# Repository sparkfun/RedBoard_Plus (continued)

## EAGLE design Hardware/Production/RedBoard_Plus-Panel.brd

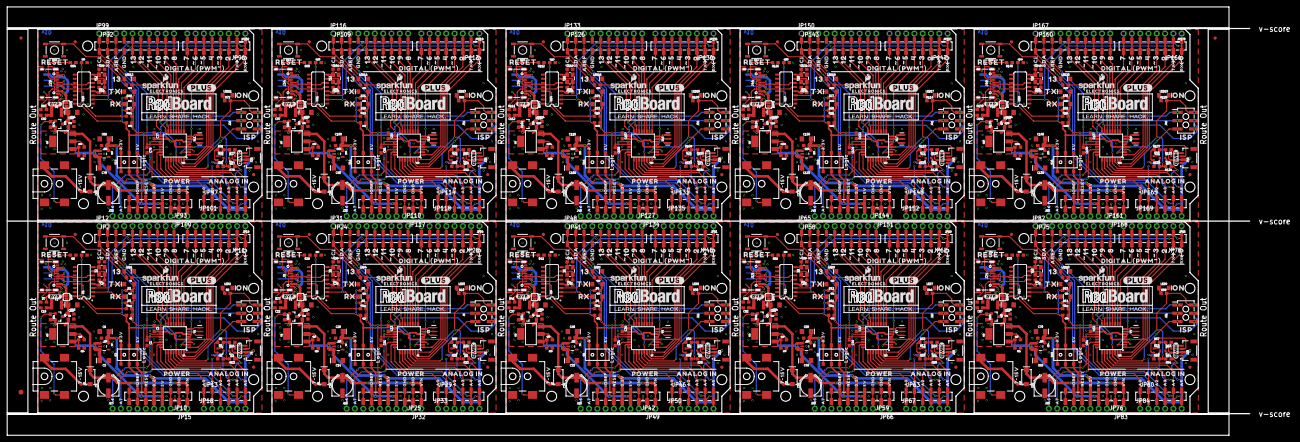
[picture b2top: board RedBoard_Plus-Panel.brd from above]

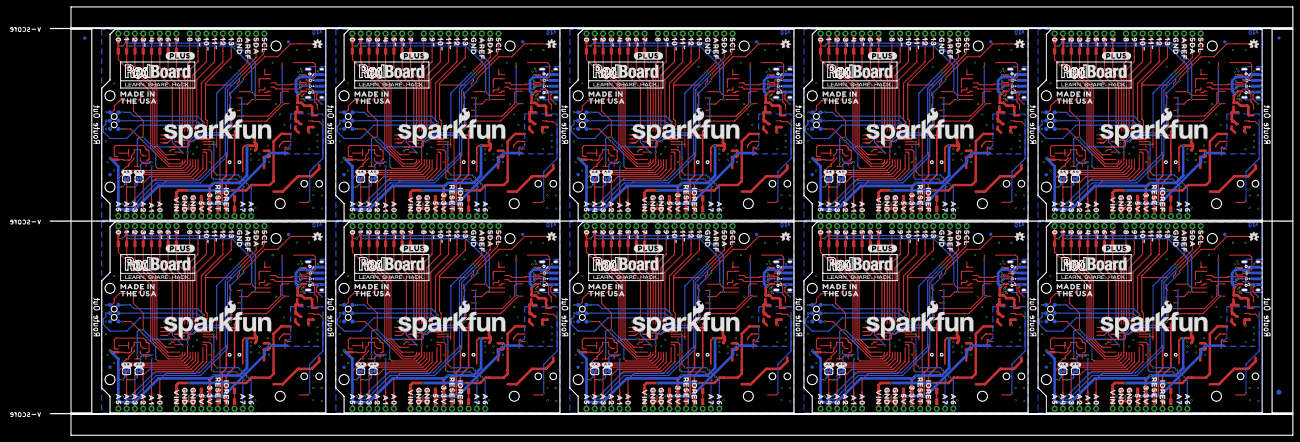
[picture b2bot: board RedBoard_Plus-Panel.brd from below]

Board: 2 copper layers, 380.2 x 131.1 mm, 1786 parts (573 on the bottom side), 530 nets.

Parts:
BYP, BYP1, BYP2, BYP3, BYP4, BYP5, BYP6, BYP7, BYP8, BYP9: JUMPER-SMT_2_NO_SILK; SMT-JUMPER_2_NO_SILK
C1, C2, C4, C8, C10, C11, C12, C13, C18, C19, C21, C22, C23, C28, C31, C32, C34, C36, C37, C38, C43, C46, C47, C49, C51, C52, C53, C58, C61, C62, C64, C66, C67, C68, C73, C76, C77, C79, C81, C82, C83, C88, C91, C92, C94, C96, C97, C98, C103, C106, C107, C109, C111, C112, C113, C118, C121, C122, C124, C126, C127, C128, C133, C136, C137, C139, C141, C142, C143, C148: 0.1uF; 0603
C3, C6, C14, C15, C24, C25, C33, C39, C40, C48, C54, C55, C63, C69, C70, C78, C84, C85, C93, C99, C100, C108, C114, C115, C123, C129, C130, C138, C144, C145: 10uF; EIA3216
C5, C20, C35, C50, C65, C80, C95, C110, C125, C140: 47uF; PANASONIC_D
C7, C9, C29, C30, C44, C45, C59, C60, C74, C75, C89, C90, C104, C105, C119, C120, C134, C135, C149, C150: 10pF; 0603
C16, C26, C41, C56, C71, C86, C101, C116, C131, C146: 1.0uF; 0603
C17, C27, C42, C57, C72, C87, C102, C117, C132, C147: 10nF; 0603
D1, D4, D7, D10, D13, D16, D19, D22, D25, D28: 1A/40V/500mV; SMA-DIODE
D2, D6, D9, D12, D15, D18, D21, D24, D27, D30: GREEN; LED-1206
D3, D5, D8, D11, D14, D17, D20, D23, D26, D29: YELLOW; LED-1206-HIDDENSILK
E$1, E$2, E$3, E$4: FIDUCIAL-1X2
E$5, E$6: FIDUCIAL-1.5X3
F1, F2, F3, F4, F5, F6, F7, F8, F9, F10: 6V/2A; 1210
FD1, FD2, FD3, FD4, FD5, FD6, FD7, FD8, FD9, FD10, FD11, FD12, FD13, FD14, FD15, FD16, FD17, FD18, FD19, FD20: FIDUCIAL1X2; FIDUCIAL-1X2
IC1, IC2, IC3, IC4, IC5, IC6, IC7, IC8, IC9, IC10: LM1117; SOT223
J1, J10, J15, J20, J25, J30, J35, J40, J45, J50: DNP; 1X02_NO_SILK
J2, J6, J11, J16, J21, J26, J31, J36, J41, J46: ISP; 2X3_SMT_POSTS
J3, J7, J12, J17, J22, J27, J32, J37, J42, J47: 5.5x2.1mm Barrel; POWER_JACK_SMD
J4, J8, J13, J18, J23, J28, J33, J38, J43, J48: QWIIC_RIGHT_ANGLE; JST04_1MM_RA
J5, J9, J14, J19, J24, J29, J34, J39, J44, J49: USB Female Type C Connector; USB-C-16P-2LAYER-PADS
JP1, JP26, JP43, JP60, JP77, JP94, JP111, JP128, JP145, JP162: SFE_LOGO_NAME.1_INCH; SFE_LOGO_NAME_.1
JP2, JP24, JP41, JP58, JP75, JP92, JP109, JP126, JP143, JP160: 1X10_SMD_COMBINED
JP3, JP4, JP5, JP6, JP16, JP17, JP20, JP21, JP35, JP36, JP37, JP38, JP52, JP53, JP54, JP55, JP69, JP70, JP71, JP72, JP86, JP87, JP88, JP89, JP103, JP104, JP105, JP106, JP120, JP121, JP122, JP123, JP137, JP138, JP139, JP140, JP154, JP155, JP156, JP157: STAND-OFFTIGHT; STAND-OFF-TIGHT
JP7, JP27, JP44, JP61, JP78, JP95, JP112, JP129, JP146, JP163: SFE_LOGO_FLAME.1_INCH; SFE_LOGO_FLAME_.1
JP8, JP9, JP22, JP23, JP39, JP40, JP56, JP57, JP73, JP74, JP90, JP91, JP107, JP108, JP124, JP125, JP141, JP142, JP158, JP159: FIDUCIAL1X2; FIDUCIAL-1X2
JP10, JP25, JP42, JP59, JP76, JP93, JP110, JP127, JP144, JP161: 1X08_SMD_COMBINED
JP11, JP28, JP45, JP62, JP79, JP96, JP113, JP130, JP147, JP164: JP11; 1X08_SMD_COMBINED
JP12, JP31, JP48, JP65, JP82, JP99, JP116, JP133, JP150, JP167: DNP; 1X10_NO_SILK
JP13, JP29, JP46, JP63, JP80, JP97, JP114, JP131, JP148, JP165: 1X06_SMD_STRAIGHT_COMBO
JP14, JP30, JP47, JP64, JP81, JP98, JP115, JP132, JP149, JP166: USB_SOLDER_PADS; USB-SOLDER-PADS
JP15, JP19, JP32, JP34, JP49, JP51, JP66, JP68, JP83, JP85, JP100, JP102, JP117, JP119, JP134, JP136, JP151, JP153, JP168, JP170: DNP; 1X08_NO_SILK
JP18, JP33, JP50, JP67, JP84, JP101, JP118, JP135, JP152, JP169: DNP; 1X06_NO_SILK
LED1, LED4, LED6, LED8, LED10, LED12, LED14, LED16, LED18, LED20: Blue; LED-1206-HIDDENSILK
LED2, LED3, LED5, LED7, LED9, LED11, LED13, LED15, LED17, LED19: GREEN; LED-1206
LOGO1, LOGO2, LOGO3, LOGO4, LOGO5, LOGO6, LOGO7, LOGO8, LOGO9, LOGO10: QWIIC_LOGO_5MM; QWIIC_5MM
Q1, Q4, Q7, Q10, Q13, Q16, Q19, Q22, Q25, Q28: 20V/4.2A/52mΩ/1.4W; SOT23-3
Q2, Q3, Q5, Q6, Q8, Q9, Q11, Q12, Q14, Q15, Q17, Q18, Q20, Q21, Q23, Q24, Q26, Q27, Q29, Q30: 310mA/60V/1.6Ω; SOT323
QW1, QW2, QW3, QW4, QW5, QW6, QW7, QW8, QW9, QW10, QW11, QW12, QW13, QW14, QW15, QW16, QW17, QW18, QW19, QW20: JUMPER-SMT_2_NC_TRACE_SILK; SMT-JUMPER_2_NC_TRACE_SILK
R1, R9, R12, R16, R23, R24, R29, R37, R38, R43, R51, R52, R57, R65, R66, R71, R79, R80, R85, R93, R94, R99, R107, R108, R113, R121, R122, R127, R135, R136: 4.7k; 0603
R2, R3, R4, R10, R17, R18, R30, R31, R32, R44, R45, R46, R58, R59, R60, R72, R73, R74, R86, R87, R88, R100, R101, R102, R114, R115, R116, R128, R129, R130: 10k; 0603
R5, R6, R11, R13, R21, R22, R25, R26, R35, R36, R39, R40, R49, R50, R53, R54, R63, R64, R67, R68, R77, R78, R81, R82, R91, R92, R95, R96, R105, R106, R109, R110, R119, R120, R123, R124, R133, R134, R137, R138: 2.2k; 0603
R7, R8, R27, R28, R41, R42, R55, R56, R69, R70, R83, R84, R97, R98, R111, R112, R125, R126, R139, R140: 5.1k; 0603
R14, R19, R33, R47, R61, R75, R89, R103, R117, R131: 715; 0603
R15, R20, R34, R48, R62, R76, R90, R104, R118, R132: 240; 0603
S1, S3, S5, S7, S9, S11, S13, S15, S17, S19: Tall Switch; TACTILE_SWITCH_SMD_5.2MM
S2, S4, S6, S8, S10, S12, S14, S16, S18, S20: SWITCH_DPDT_SMD_AYZ0202
TP1, TP2, TP3, TP4, TP5, TP6, TP7, TP8, TP9, TP10, TP11, TP12, TP13, TP14, TP15, TP16, TP17, TP18, TP19, TP20, TP21, TP22, TP23, TP24, TP25, TP26, TP27, TP28, TP29, TP30, TP31, TP32, TP33, TP34, TP35, TP36, TP37, TP38, TP39, TP40, TP41, TP42, TP43, TP44, TP45, TP46, TP47, TP48, TP49, TP50, TP51, TP52, TP53, TP54, TP55, TP56, TP57, TP58, TP59, TP60: TP-3x5; PAD.03X.05
U1, U6, U9, U12, U15, U18, U21, U24, U27, U30: CH340G; SO016
U2, U4, U7, U10, U13, U16, U19, U22, U25, U28: ATMEGA328P_TQFP; TQFP32-08
U3, U5, U8, U11, U14, U17, U20, U23, U26, U29: 3.3V; SOT23-5
U$1, U$3, U$164, U$165, U$262, U$263, U$360, U$361, U$458, U$459, U$556, U$557, U$654, U$655, U$752, U$753, U$850, U$851, U$948, U$949: REDBOARD_LOGO
U$2, U$162, U$260, U$358, U$456, U$554, U$652, U$750, U$848, U$946: _D#0
U$4, U$160, U$258, U$356, U$454, U$552, U$650, U$748, U$846, U$944: V0
U$5, U$16, U$197, U$295, U$393, U$491, U$589, U$687, U$785, U$883: OSHW-LOGOS; OSHW-LOGO-S
U$6, U$14, U$198, U$296, U$394, U$492, U$590, U$688, U$786, U$884: #BYP#0
U$7, U$17, U$199, U$297, U$395, U$493, U$591, U$689, U$787, U$885: 7#15V0
U$8, U$22, U$77, U$154, U$200, U$252, U$298, U$350, U$396, U$448, U$494, U$546, U$592, U$644, U$690, U$742, U$788, U$840, U$886, U$938: 130
U$9, U$195, U$293, U$391, U$489, U$587, U$685, U$783, U$881, U$979: 10#0
U$10, U$163, U$261, U$359, U$457, U$555, U$653, U$751, U$849, U$947: G0
U$11, U$190, U$288, U$386, U$484, U$582, U$680, U$778, U$876, U$974: LOGIC0
U$12, U$161, U$259, U$357, U$455, U$553, U$651, U$749, U$847, U$945: D#0
U$13, U$95, U$177, U$181, U$275, U$279, U$373, U$377, U$471, U$475, U$569, U$573, U$667, U$671, U$765, U$769, U$863, U$867, U$961, U$965: _RESET0
U$15, U$23, U$76, U$153, U$201, U$251, U$299, U$349, U$397, U$447, U$495, U$545, U$593, U$643, U$691, U$741, U$789, U$839, U$887, U$937: 120
U$18, U$182, U$280, U$378, U$476, U$574, U$672, U$770, U$868, U$966: _AREF0
U$19, U$183, U$281, U$379, U$477, U$575, U$673, U$771, U$869, U$967: _SCL0
U$20, U$184, U$282, U$380, U$478, U$576, U$674, U$772, U$870, U$968: _SDA0
U$21, U$196, U$294, U$392, U$490, U$588, U$686, U$784, U$882, U$980: 11#0
U$24, U$74, U$202, U$300, U$398, U$496, U$594, U$692, U$790, U$888: #110
U$25, U$75, U$203, U$301, U$399, U$497, U$595, U$693, U$791, U$889: #100
U$26, U$91, U$204, U$302, U$400, U$498, U$596, U$694, U$792, U$890: #90
U$27, U$72, U$92, U$151, U$205, U$249, U$303, U$347, U$401, U$445, U$499, U$543, U$597, U$641, U$695, U$739, U$793, U$837, U$891, U$935: 80
U$28, U$71, U$108, U$150, U$206, U$248, U$304, U$346, U$402, U$444, U$500, U$542, U$598, U$640, U$696, U$738, U$794, U$836, U$892, U$934: 70
U$29, U$109, U$207, U$305, U$403, U$501, U$599, U$697, U$795, U$893: #60
U$30, U$110, U$208, U$306, U$404, U$502, U$600, U$698, U$796, U$894: #50
U$31, U$68, U$111, U$147, U$209, U$245, U$307, U$343, U$405, U$441, U$503, U$539, U$601, U$637, U$699, U$735, U$797, U$833, U$895, U$931: 40
U$32, U$112, U$210, U$308, U$406, U$504, U$602, U$700, U$798, U$896: #30
U$33, U$66, U$113, U$145, U$211, U$243, U$309, U$341, U$407, U$439, U$505, U$537, U$603, U$635, U$701, U$733, U$799, U$831, U$897, U$929: 20
U$34, U$65, U$114, U$144, U$212, U$242, U$310, U$340, U$408, U$438, U$506, U$536, U$604, U$634, U$702, U$732, U$800, U$830, U$898, U$928: 10
U$35, U$64, U$115, U$143, U$213, U$241, U$311, U$339, U$409, U$437, U$507, U$535, U$605, U$633, U$703, U$731, U$801, U$829, U$899, U$927: 00
U$36, U$116, U$214, U$312, U$410, U$508, U$606, U$704, U$802, U$900: TX0
U$37, U$117, U$215, U$313, U$411, U$509, U$607, U$705, U$803, U$901: RX0
U$38, U$118, U$216, U$314, U$412, U$510, U$608, U$706, U$804, U$902: DIGITAL_##PWM####_0
U$39, U$119, U$217, U$315, U$413, U$511, U$609, U$707, U$805, U$903: 13_0
U$40, U$120, U$218, U$316, U$414, U$512, U$610, U$708, U$806, U$904: _TX0
U$41, U$121, U$219, U$317, U$415, U$513, U$611, U$709, U$807, U$905: _RX0
U$42, U$191, U$289, U$387, U$485, U$583, U$681, U$779, U$877, U$975: _GND0
U$43, U$51, U$122, U$130, U$220, U$228, U$318, U$326, U$416, U$424, U$514, U$522, U$612, U$620, U$710, U$718, U$808, U$816, U$906, U$914: 3#3V0
U$44, U$52, U$123, U$131, U$221, U$229, U$319, U$327, U$417, U$425, U$515, U$523, U$613, U$621, U$711, U$719, U$809, U$817, U$907, U$915: 5V0
U$45, U$124, U$222, U$320, U$418, U$516, U$614, U$712, U$810, U$908: ON0
U$46, U$125, U$223, U$321, U$419, U$517, U$615, U$713, U$811, U$909: ISP0
U$47, U$126, U$224, U$322, U$420, U$518, U$616, U$714, U$812, U$910: POWER0
U$48, U$127, U$225, U$323, U$421, U$519, U$617, U$715, U$813, U$911: ANALOG_IN0
U$49, U$128, U$226, U$324, U$422, U$520, U$618, U$716, U$814, U$912: IOREF0
U$50, U$129, U$227, U$325, U$423, U$521, U$619, U$717, U$815, U$913: RESET0
U$53, U$54, U$132, U$133, U$230, U$231, U$328, U$329, U$426, U$427, U$524, U$525, U$622, U$623, U$720, U$721, U$818, U$819, U$916, U$917: GND0
U$55, U$134, U$232, U$330, U$428, U$526, U$624, U$722, U$820, U$918: VIN0
U$56, U$135, U$233, U$331, U$429, U$527, U$625, U$723, U$821, U$919: A00
U$57, U$136, U$234, U$332, U$430, U$528, U$626, U$724, U$822, U$920: A10
U$58, U$137, U$235, U$333, U$431, U$529, U$627, U$725, U$823, U$921: A20
U$59, U$138, U$236, U$334, U$432, U$530, U$628, U$726, U$824, U$922: A30
U$60, U$139, U$237, U$335, U$433, U$531, U$629, U$727, U$825, U$923: A40
U$61, U$140, U$238, U$336, U$434, U$532, U$630, U$728, U$826, U$924: A50
U$62, U$141, U$239, U$337, U$435, U$533, U$631, U$729, U$827, U$925: A60
U$63, U$142, U$240, U$338, U$436, U$534, U$632, U$730, U$828, U$926: A70
U$67, U$146, U$244, U$342, U$440, U$538, U$636, U$734, U$832, U$930: 3#0
U$69, U$148, U$246, U$344, U$442, U$540, U$638, U$736, U$834, U$932: 5#0
U$70, U$149, U$247, U$345, U$443, U$541, U$639, U$737, U$835, U$933: 6#0
U$73, U$152, U$250, U$348, U$446, U$544, U$642, U$740, U$838, U$936: 9#0
U$78, U$166, U$264, U$362, U$460, U$558, U$656, U$754, U$852, U$950: SFE_LOGO_NAME_.3
U$79, U$155, U$253, U$351, U$449, U$547, U$645, U$743, U$841, U$939: AREF0
U$80, U$156, U$254, U$352, U$450, U$548, U$646, U$744, U$842, U$940: SDA0
U$81, U$157, U$255, U$353, U$451, U$549, U$647, U$745, U$843, U$941: SCL0
U$82, U$158, U$256, U$354, U$452, U$550, U$648, U$746, U$844, U$942: MADE_IN0
U$83, U$159, U$257, U$355, U$453, U$551, U$649, U$747, U$845, U$943: THE_USA0
U$84, U$169, U$267, U$365, U$463, U$561, U$659, U$757, U$855, U$953: _A40
U$85, U$99, U$107, U$192, U$193, U$194, U$290, U$291, U$292, U$388, U$389, U$390, U$486, U$487, U$488, U$584, U$585, U$586, U$682, U$683, U$684, U$780, U$781, U$782, U$878, U$879, U$880, U$976, U$977, U$978: _GND_0
U$86, U$170, U$268, U$366, U$464, U$562, U$660, U$758, U$856, U$954: _A30
U$87, U$171, U$269, U$367, U$465, U$563, U$661, U$759, U$857, U$955: _A20
U$88, U$172, U$270, U$368, U$466, U$564, U$662, U$760, U$858, U$956: _A10
U$89, U$173, U$271, U$369, U$467, U$565, U$663, U$761, U$859, U$957: _A00
U$90, U$174, U$272, U$370, U$468, U$566, U$664, U$762, U$860, U$958: _VIN0
U$93, U$175, U$273, U$371, U$469, U$567, U$665, U$763, U$861, U$959: _5V0
U$94, U$176, U$274, U$372, U$470, U$568, U$666, U$764, U$862, U$960: _3#3V0
U$96, U$178, U$276, U$374, U$472, U$570, U$668, U$766, U$864, U$962: _IOREF0
U$97, U$179, U$277, U$375, U$473, U$571, U$669, U$767, U$865, U$963: _A60
U$98, U$180, U$278, U$376, U$474, U$572, U$670, U$768, U$866, U$964: _A70
U$100, U$103, U$185, U$186, U$283, U$284, U$381, U$382, U$479, U$480, U$577, U$578, U$675, U$676, U$773, U$774, U$871, U$872, U$969, U$970: #PLUS#0
U$101, U$167, U$265, U$363, U$461, U$559, U$657, U$755, U$853, U$951: SFE_LOGO_FLAME_.2
U$102, U$168, U$266, U$364, U$462, U$560, U$658, U$756, U$854, U$952: _A50
U$104, U$187, U$285, U$383, U$481, U$579, U$677, U$775, U$873, U$971: ELECTRONICS0
U$105, U$188, U$286, U$384, U$482, U$580, U$678, U$776, U$874, U$972: #A4#0
U$106, U$189, U$287, U$385, U$483, U$581, U$679, U$777, U$875, U$973: #A5#0
Y1, Y3, Y5, Y7, Y9, Y11, Y13, Y15, Y17, Y19: 16MHz; RESONATOR-SMD-3.2X1.3
Y2, Y4, Y6, Y8, Y10, Y12, Y14, Y16, Y18, Y20: 12MHz; CRYSTAL-SMD-3.2X2.5MM

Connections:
3.3V: C6.+, C16.1, J4.2, JP10.5, JP15.5, Q2.1, Q3.1, R5.2, R11.2, S2.1, S2.4, U3.5
3.3V1: C25.+, C26.1, J8.2, JP25.5, JP32.5, Q5.1, Q6.1, R21.2, R25.2, S4.1, S4.4, U5.5
3.3V2: C40.+, C41.1, J13.2, JP42.5, JP49.5, Q8.1, Q9.1, R35.2, R39.2, S6.1, S6.4, U8.5
3.3V3: C55.+, C56.1, J18.2, JP59.5, JP66.5, Q11.1, Q12.1, R49.2, R53.2, S8.1, S8.4, U11.5
3.3V4: C70.+, C71.1, J23.2, JP76.5, JP83.5, Q14.1, Q15.1, R63.2, R67.2, S10.1, S10.4, U14.5
3.3V5: C85.+, C86.1, J28.2, JP93.5, JP100.5, Q17.1, Q18.1, R77.2, R81.2, S12.1, S12.4, U17.5
3.3V6: C100.+, C101.1, J33.2, JP110.5, JP117.5, Q20.1, Q21.1, R91.2, R95.2, S14.1, S14.4, U20.5
3.3V7: C115.+, C116.1, J38.2, JP127.5, JP134.5, Q23.1, Q24.1, R105.2, R109.2, S16.1, S16.4, U23.5
3.3V8: C130.+, C131.1, J43.2, JP144.5, JP151.5, Q26.1, Q27.1, R119.2, R123.2, S18.1, S18.4, U26.5
3.3V9: C145.+, C146.1, J48.2, JP161.5, JP168.5, Q29.1, Q30.1, R133.2, R137.2, S20.1, S20.4, U29.5
5V: C3.+, C4.1, IC3.2, IC3.4, JP10.4, JP15.4, Q1.2, R4.2, R15.2, S2.3, S2.6, U3.1, U3.3
5V1: C14.+, C19.1, IC1.2, IC1.4, JP25.4, JP32.4, Q4.2, R18.2, R20.2, S4.3, S4.6, U5.1, U5.3
5V2: C33.+, C34.1, IC2.2, IC2.4, JP42.4, JP49.4, Q7.2, R32.2, R34.2, S6.3, S6.6, U8.1, U8.3
5V3: C48.+, C49.1, IC4.2, IC4.4, JP59.4, JP66.4, Q10.2, R46.2, R48.2, S8.3, S8.6, U11.1, U11.3
5V4: C63.+, C64.1, IC5.2, IC5.4, JP76.4, JP83.4, Q13.2, R60.2, R62.2, S10.3, S10.6, U14.1, U14.3
5V5: C78.+, C79.1, IC6.2, IC6.4, JP93.4, JP100.4, Q16.2, R74.2, R76.2, S12.3, S12.6, U17.1, U17.3
5V6: C93.+, C94.1, IC7.2, IC7.4, JP110.4, JP117.4, Q19.2, R88.2, R90.2, S14.3, S14.6, U20.1, U20.3
5V7: C108.+, C109.1, IC8.2, IC8.4, JP127.4, JP134.4, Q22.2, R102.2, R104.2, S16.3, S16.6, U23.1, U23.3
5V8: C123.+, C124.1, IC9.2, IC9.4, JP144.4, JP151.4, Q25.2, R116.2, R118.2, S18.3, S18.6, U26.1, U26.3
5V9: C138.+, C139.1, IC10.2, IC10.4, JP161.4, JP168.4, Q28.2, R130.2, R132.2, S20.3, S20.6, U29.1, U29.3
!DTR!: C8.1, U1.13
!DTR!1: C21.1, U6.13
!DTR!2: C36.1, U9.13
!DTR!3: C51.1, U12.13
!DTR!4: C66.1, U15.13
!DTR!5: C81.1, U18.13
!DTR!6: C96.1, U21.13
!DTR!7: C111.1, U24.13
!DTR!8: C126.1, U27.13
!DTR!9: C141.1, U30.13
!RESET: C8.2, J2.5, JP10.6, JP15.6, R3.1, S1.3, S1.4, TP6.P$1, U4.29
!RESET1: C21.2, J6.5, JP25.6, JP32.6, R17.1, S3.3, S3.4, TP12.P$1, U2.29
!RESET2: C36.2, J11.5, JP42.6, JP49.6, R31.1, S5.3, S5.4, TP18.P$1, U7.29
!RESET3: C51.2, J16.5, JP59.6, JP66.6, R45.1, S7.3, S7.4, TP24.P$1, U10.29
!RESET4: C66.2, J21.5, JP76.6, JP83.6, R59.1, S9.3, S9.4, TP30.P$1, U13.29
!RESET5: C81.2, J26.5, JP93.6, JP100.6, R73.1, S11.3, S11.4, TP36.P$1, U16.29
!RESET6: C96.2, J31.5, JP110.6, JP117.6, R87.1, S13.3, S13.4, TP42.P$1, U19.29
!RESET7: C111.2, J36.5, JP127.6, JP134.6, R101.1, S15.3, S15.4, TP48.P$1, U22.29
!RESET8: C126.2, J41.5, JP144.6, JP151.6, R115.1, S17.3, S17.4, TP54.P$1, U25.29
!RESET9: C141.2, J46.5, JP161.6, JP168.6, R129.1, S19.3, S19.4, TP60.P$1, U28.29
A0: JP13.1, JP18.1, U4.23
A1: JP13.2, JP18.2, U4.24
A2: JP13.3, JP18.3, U4.25
A3: JP13.4, JP18.4, U4.26
A4: JP29.1, JP33.1, U2.23
A4/SDA: JP2.2A, JP2.2B, JP12.2, JP13.5, JP18.5, QW2.1, U4.27
A4/SDA1: JP24.2A, JP24.2B, JP29.5, JP31.2, JP33.5, QW3.1, U2.27
A4/SDA2: JP41.2A, JP41.2B, JP46.5, JP48.2, JP50.5, QW5.1, U7.27
A4/SDA3: JP58.2A, JP58.2B, JP63.5, JP65.2, JP67.5, QW7.1, U10.27
A4/SDA4: JP75.2A, JP75.2B, JP80.5, JP82.2, JP84.5, QW9.1, U13.27
A4/SDA5: JP92.2A, JP92.2B, JP97.5, JP99.2, JP101.5, QW11.1, U16.27
A4/SDA6: JP109.2A, JP109.2B, JP114.5, JP116.2, JP118.5, QW13.1, U19.27
A4/SDA7: JP126.2A, JP126.2B, JP131.5, JP133.2, JP135.5, QW15.1, U22.27
A4/SDA8: JP143.2A, JP143.2B, JP148.5, JP150.2, JP152.5, QW17.1, U25.27
A4/SDA9: JP160.2A, JP160.2B, JP165.5, JP167.2, JP169.5, QW19.1, U28.27
A5: JP29.2, JP33.2, U2.24
A5/SCL: JP2.1A, JP2.1B, JP12.1, JP13.6, JP18.6, QW1.1, U4.28
A5/SCL1: JP24.1A, JP24.1B, JP29.6, JP31.1, JP33.6, QW4.1, U2.28
A5/SCL2: JP41.1A, JP41.1B, JP46.6, JP48.1, JP50.6, QW6.1, U7.28
A5/SCL3: JP58.1A, JP58.1B, JP63.6, JP65.1, JP67.6, QW8.1, U10.28
A5/SCL4: JP75.1A, JP75.1B, JP80.6, JP82.1, JP84.6, QW10.1, U13.28
A5/SCL5: JP92.1A, JP92.1B, JP97.6, JP99.1, JP101.6, QW12.1, U16.28
A5/SCL6: JP109.1A, JP109.1B, JP114.6, JP116.1, JP118.6, QW14.1, U19.28
A5/SCL7: JP126.1A, JP126.1B, JP131.6, JP133.1, JP135.6, QW16.1, U22.28
A5/SCL8: JP143.1A, JP143.1B, JP148.6, JP150.1, JP152.6, QW18.1, U25.28
A5/SCL9: JP160.1A, JP160.1B, JP165.6, JP167.1, JP169.6, QW20.1, U28.28
A6: J1.1, U4.19
A7: J1.2, U4.22
A8: JP29.3, JP33.3, U2.25
A9: JP29.4, JP33.4, U2.26
A10: J10.1, U2.19
A11: J10.2, U2.22
A12: JP46.1, JP50.1, U7.23
A13: JP46.2, JP50.2, U7.24
A14: JP46.3, JP50.3, U7.25
A15: JP46.4, JP50.4, U7.26
A16: J15.1, U7.19
A17: J15.2, U7.22
A18: JP63.1, JP67.1, U10.23
A19: JP63.2, JP67.2, U10.24
A20: JP63.3, JP67.3, U10.25
A21: JP63.4, JP67.4, U10.26
A22: J20.1, U10.19
A23: J20.2, U10.22
A24: JP80.1, JP84.1, U13.23
A25: JP80.2, JP84.2, U13.24
A26: JP80.3, JP84.3, U13.25
A27: JP80.4, JP84.4, U13.26
A28: J25.1, U13.19
A29: J25.2, U13.22
A30: JP97.1, JP101.1, U16.23
A31: JP97.2, JP101.2, U16.24
A32: JP97.3, JP101.3, U16.25
A33: JP97.4, JP101.4, U16.26
A34: J30.1, U16.19
A35: J30.2, U16.22
A36: JP114.1, JP118.1, U19.23
A37: JP114.2, JP118.2, U19.24
A38: JP114.3, JP118.3, U19.25
A39: JP114.4, JP118.4, U19.26
A40: J35.1, U19.19
A41: J35.2, U19.22
A42: JP131.1, JP135.1, U22.23
A43: JP131.2, JP135.2, U22.24
A44: JP131.3, JP135.3, U22.25
A45: JP131.4, JP135.4, U22.26
A46: J40.1, U22.19
A47: J40.2, U22.22
A48: JP148.1, JP152.1, U25.23
A49: JP148.2, JP152.2, U25.24
A50: JP148.3, JP152.3, U25.25
A51: JP148.4, JP152.4, U25.26
A52: J45.1, U25.19
A53: J45.2, U25.22
A54: JP165.1, JP169.1, U28.23
A55: JP165.2, JP169.2, U28.24
A56: JP165.3, JP169.3, U28.25
A57: JP165.4, JP169.4, U28.26
A58: J50.1, U28.19
A59: J50.2, U28.22
AREF: C1.1, JP2.3A, JP2.3B, JP12.3, U4.20
AREF1: C11.1, JP24.3A, JP24.3B, JP31.3, U2.20
AREF2: C31.1, JP41.3A, JP41.3B, JP48.3, U7.20
AREF3: C46.1, JP58.3A, JP58.3B, JP65.3, U10.20
AREF4: C61.1, JP75.3A, JP75.3B, JP82.3, U13.20
AREF5: C76.1, JP92.3A, JP92.3B, JP99.3, U16.20
AREF6: C91.1, JP109.3A, JP109.3B, JP116.3, U19.20
AREF7: C106.1, JP126.3A, JP126.3B, JP133.3, U22.20
AREF8: C121.1, JP143.3A, JP143.3B, JP150.3, U25.20
AREF9: C136.1, JP160.3A, JP160.3B, JP167.3, U28.20
CC1: J5.A5, R8.2
CC2: J5.B5, R7.2
CC3: J9.B5, R27.2
CC4: J9.A5, R28.2
CC5: J14.B5, R41.2
CC6: J14.A5, R42.2
CC7: J19.B5, R55.2
CC8: J19.A5, R56.2
CC9: J24.B5, R69.2
CC10: J24.A5, R70.2
CC11: J29.B5, R83.2
CC12: J29.A5, R84.2
CC13: J34.B5, R97.2
CC14: J34.A5, R98.2
CC15: J39.B5, R111.2
CC16: J39.A5, R112.2
CC17: J44.B5, R125.2
CC18: J44.A5, R126.2
CC19: J49.B5, R139.2
CC20: J49.A5, R140.2
CIPO: J2.1, JP2.6A, JP2.6B, JP12.6, TP4.P$1, U4.16
CIPO1: J6.1, JP24.6A, JP24.6B, JP31.6, TP10.P$1, U2.16
CIPO2: J11.1, JP41.6A, JP41.6B, JP48.6, TP16.P$1, U7.16
CIPO3: J16.1, JP58.6A, JP58.6B, JP65.6, TP22.P$1, U10.16
CIPO4: J21.1, JP75.6A, JP75.6B, JP82.6, TP28.P$1, U13.16
CIPO5: J26.1, JP92.6A, JP92.6B, JP99.6, TP34.P$1, U16.16
CIPO6: J31.1, JP109.6A, JP109.6B, JP116.6, TP40.P$1, U19.16
CIPO7: J36.1, JP126.6A, JP126.6B, JP133.6, TP46.P$1, U22.16
CIPO8: J41.1, JP143.6A, JP143.6B, JP150.6, TP52.P$1, U25.16
CIPO9: J46.1, JP160.6A, JP160.6B, JP167.6, TP58.P$1, U28.16
COPI: J2.4, JP2.7A, JP2.7B, JP12.7, TP2.P$1, U4.15
COPI1: J6.4, JP24.7A, JP24.7B, JP31.7, TP8.P$1, U2.15
COPI2: J11.4, JP41.7A, JP41.7B, JP48.7, TP14.P$1, U7.15
COPI3: J16.4, JP58.7A, JP58.7B, JP65.7, TP20.P$1, U10.15
COPI4: J21.4, JP75.7A, JP75.7B, JP82.7, TP26.P$1, U13.15
COPI5: J26.4, JP92.7A, JP92.7B, JP99.7, TP32.P$1, U16.15
COPI6: J31.4, JP109.7A, JP109.7B, JP116.7, TP38.P$1, U19.15
COPI7: J36.4, JP126.7A, JP126.7B, JP133.7, TP44.P$1, U22.15
COPI8: J41.4, JP143.7A, JP143.7B, JP150.7, TP50.P$1, U25.15
COPI9: J46.4, JP160.7A, JP160.7B, JP167.7, TP56.P$1, U28.15
D1: JP28.3, JP34.3, U2.32
D2: JP11.3, JP19.3, U4.32
D3: JP11.4, JP19.4, U4.1
D4: JP11.5, JP19.5, U4.2
D5: JP11.6, JP19.6, U4.9
D6: JP11.7, JP19.7, U4.10
D7: JP11.8, JP19.8, U4.11
D8: JP2.10A, JP2.10B, JP12.10, U4.12
D9: JP2.9A, JP2.9B, JP12.9, U4.13
D10: JP2.8A, JP2.8B, JP12.8, U4.14
D11: JP28.4, JP34.4, U2.1
D12: JP28.5, JP34.5, U2.2
D13: JP28.6, JP34.6, U2.9
D14: JP28.7, JP34.7, U2.10
D15: JP28.8, JP34.8, U2.11
D16: JP24.10A, JP24.10B, JP31.10, U2.12
D17: JP24.9A, JP24.9B, JP31.9, U2.13
D18: JP24.8A, JP24.8B, JP31.8, U2.14
D19: JP45.3, JP51.3, U7.32
D20: JP45.4, JP51.4, U7.1
D21: JP45.5, JP51.5, U7.2
D22: JP45.6, JP51.6, U7.9
D23: JP45.7, JP51.7, U7.10
D24: JP45.8, JP51.8, U7.11
D25: JP41.10A, JP41.10B, JP48.10, U7.12
D26: JP41.9A, JP41.9B, JP48.9, U7.13
D27: JP41.8A, JP41.8B, JP48.8, U7.14
D28: JP62.3, JP68.3, U10.32
D29: JP62.4, JP68.4, U10.1
D30: JP62.5, JP68.5, U10.2
D31: JP62.6, JP68.6, U10.9
D32: JP62.7, JP68.7, U10.10
D33: JP62.8, JP68.8, U10.11
D34: JP58.10A, JP58.10B, JP65.10, U10.12
D35: JP58.9A, JP58.9B, JP65.9, U10.13
D36: JP58.8A, JP58.8B, JP65.8, U10.14
D37: JP79.3, JP85.3, U13.32
D38: JP79.4, JP85.4, U13.1
D39: JP79.5, JP85.5, U13.2
D40: JP79.6, JP85.6, U13.9
D41: JP79.7, JP85.7, U13.10
D42: JP79.8, JP85.8, U13.11
D43: JP75.10A, JP75.10B, JP82.10, U13.12
D44: JP75.9A, JP75.9B, JP82.9, U13.13
D45: JP75.8A, JP75.8B, JP82.8, U13.14
D46: JP96.3, JP102.3, U16.32
D47: JP96.4, JP102.4, U16.1
D48: JP96.5, JP102.5, U16.2
D49: JP96.6, JP102.6, U16.9
D50: JP96.7, JP102.7, U16.10
D51: JP96.8, JP102.8, U16.11
D52: JP92.10A, JP92.10B, JP99.10, U16.12
D53: JP92.9A, JP92.9B, JP99.9, U16.13
D54: JP92.8A, JP92.8B, JP99.8, U16.14
D55: JP113.3, JP119.3, U19.32
D56: JP113.4, JP119.4, U19.1
D57: JP113.5, JP119.5, U19.2
D58: JP113.6, JP119.6, U19.9
D59: JP113.7, JP119.7, U19.10
D60: JP113.8, JP119.8, U19.11
D61: JP109.10A, JP109.10B, JP116.10, U19.12
D62: JP109.9A, JP109.9B, JP116.9, U19.13
D63: JP109.8A, JP109.8B, JP116.8, U19.14
D64: JP130.3, JP136.3, U22.32
D65: JP130.4, JP136.4, U22.1
D66: JP130.5, JP136.5, U22.2
D67: JP130.6, JP136.6, U22.9
D68: JP130.7, JP136.7, U22.10
D69: JP130.8, JP136.8, U22.11
D70: JP126.10A, JP126.10B, JP133.10, U22.12
D71: JP126.9A, JP126.9B, JP133.9, U22.13
D72: JP126.8A, JP126.8B, JP133.8, U22.14
D73: JP147.3, JP153.3, U25.32
D74: JP147.4, JP153.4, U25.1
D75: JP147.5, JP153.5, U25.2
D76: JP147.6, JP153.6, U25.9
D77: JP147.7, JP153.7, U25.10
D78: JP147.8, JP153.8, U25.11
D79: JP143.10A, JP143.10B, JP150.10, U25.12
D80: JP143.9A, JP143.9B, JP150.9, U25.13
D81: JP143.8A, JP143.8B, JP150.8, U25.14
D82: JP164.3, JP170.3, U28.32
D83: JP164.4, JP170.4, U28.1
D84: JP164.5, JP170.5, U28.2
D85: JP164.6, JP170.6, U28.9
D86: JP164.7, JP170.7, U28.10
D87: JP164.8, JP170.8, U28.11
D88: JP160.10A, JP160.10B, JP167.10, U28.12
D89: JP160.9A, JP160.9B, JP167.9, U28.13
D90: JP160.8A, JP160.8B, JP167.8, U28.14
D+: J5.A6, J5.B6, JP14.D+, U1.5
D+1: J9.A6, J9.B6, JP30.D+, U6.5
D+2: J14.A6, J14.B6, JP47.D+, U9.5
D+3: J19.A6, J19.B6, JP64.D+, U12.5
D+4: J24.A6, J24.B6, JP81.D+, U15.5
D+5: J29.A6, J29.B6, JP98.D+, U18.5
D+6: J34.A6, J34.B6, JP115.D+, U21.5
D+7: J39.A6, J39.B6, JP132.D+, U24.5
D+8: J44.A6, J44.B6, JP149.D+, U27.5
D+9: J49.A6, J49.B6, JP166.D+, U30.5
D-: J5.A7, J5.B7, JP14.D-, U1.6
D-1: J9.A7, J9.B7, JP30.D-, U6.6
D-2: J14.A7, J14.B7, JP47.D-, U9.6
D-3: J19.A7, J19.B7, JP64.D-, U12.6
D-4: J24.A7, J24.B7, JP81.D-, U15.6
D-5: J29.A7, J29.B7, JP98.D-, U18.6
D-6: J34.A7, J34.B7, JP115.D-, U21.6
D-7: J39.A7, J39.B7, JP132.D-, U24.6
D-8: J44.A7, J44.B7, JP149.D-, U27.6
D-9: J49.A7, J49.B7, JP166.D-, U30.6
GND: C1.2, C2.1, C3.-, C4.2, C5.-, C6.-, C7.2, C9.2, C10.2, C12.2, C15.-, C16.2, C17.2, C18.2, J2.6, J3.GND, J4.1, J5.GND, J5.GND2, JP2.4A, JP2.4B, JP10.2, JP10.3, JP12.4, JP14.GND, JP15.2, JP15.3, LED1.C, LED2.C, R7.1, R8.1, R14.1, S1.1, S1.2, TP3.P$1, U1.1, U3.2, U4.3, U4.5, U4.21, Y1.2, Y2.2, Y2.4
GND1: C11.2, C13.1, C14.-, C19.2, C20.-, C22.2, C23.2, C24.-, C25.-, C26.2, C27.2, C28.2, C29.2, C30.2, J6.6, J7.GND, J8.1, J9.GND, J9.GND2, JP24.4A, JP24.4B, JP25.2, JP25.3, JP30.GND, JP31.4, JP32.2, JP32.3, LED3.C, LED4.C, R19.1, R27.1, R28.1, S3.1, S3.2, TP9.P$1, U2.3, U2.5, U2.21, U5.2, U6.1, Y3.2, Y4.2, Y4.4
GND2: C31.2, C32.1, C33.-, C34.2, C35.-, C37.2, C38.2, C39.-, C40.-, C41.2, C42.2, C43.2, C44.2, C45.2, J11.6, J12.GND, J13.1, J14.GND, J14.GND2, JP41.4A, JP41.4B, JP42.2, JP42.3, JP47.GND, JP48.4, JP49.2, JP49.3, LED5.C, LED6.C, R33.1, R41.1, R42.1, S5.1, S5.2, TP15.P$1, U7.3, U7.5, U7.21, U8.2, U9.1, Y5.2, Y6.2, Y6.4
GND3: C46.2, C47.1, C48.-, C49.2, C50.-, C52.2, C53.2, C54.-, C55.-, C56.2, C57.2, C58.2, C59.2, C60.2, J16.6, J17.GND, J18.1, J19.GND, J19.GND2, JP58.4A, JP58.4B, JP59.2, JP59.3, JP64.GND, JP65.4, JP66.2, JP66.3, LED7.C, LED8.C, R47.1, R55.1, R56.1, S7.1, S7.2, TP21.P$1, U10.3, U10.5, U10.21, U11.2, U12.1, Y7.2, Y8.2, Y8.4
GND4: C61.2, C62.1, C63.-, C64.2, C65.-, C67.2, C68.2, C69.-, C70.-, C71.2, C72.2, C73.2, C74.2, C75.2, J21.6, J22.GND, J23.1, J24.GND, J24.GND2, JP75.4A, JP75.4B, JP76.2, JP76.3, JP81.GND, JP82.4, JP83.2, JP83.3, LED9.C, LED10.C, R61.1, R69.1, R70.1, S9.1, S9.2, TP27.P$1, U13.3, U13.5, U13.21, U14.2, U15.1, Y9.2, Y10.2, Y10.4
GND5: C76.2, C77.1, C78.-, C79.2, C80.-, C82.2, C83.2, C84.-, C85.-, C86.2, C87.2, C88.2, C89.2, C90.2, J26.6, J27.GND, J28.1, J29.GND, J29.GND2, JP92.4A, JP92.4B, JP93.2, JP93.3, JP98.GND, JP99.4, JP100.2, JP100.3, LED11.C, LED12.C, R75.1, R83.1, R84.1, S11.1, S11.2, TP33.P$1, U16.3, U16.5, U16.21, U17.2, U18.1, Y11.2, Y12.2, Y12.4
GND6: C91.2, C92.1, C93.-, C94.2, C95.-, C97.2, C98.2, C99.-, C100.-, C101.2, C102.2, C103.2, C104.2, C105.2, J31.6, J32.GND, J33.1, J34.GND, J34.GND2, JP109.4A, JP109.4B, JP110.2, JP110.3, JP115.GND, JP116.4, JP117.2, JP117.3, LED13.C, LED14.C, R89.1, R97.1, R98.1, S13.1, S13.2, TP39.P$1, U19.3, U19.5, U19.21, U20.2, U21.1, Y13.2, Y14.2, Y14.4
GND7: C106.2, C107.1, C108.-, C109.2, C110.-, C112.2, C113.2, C114.-, C115.-, C116.2, C117.2, C118.2, C119.2, C120.2, J36.6, J37.GND, J38.1, J39.GND, J39.GND2, JP126.4A, JP126.4B, JP127.2, JP127.3, JP132.GND, JP133.4, JP134.2, JP134.3, LED15.C, LED16.C, R103.1, R111.1, R112.1, S15.1, S15.2, TP45.P$1, U22.3, U22.5, U22.21, U23.2, U24.1, Y15.2, Y16.2, Y16.4
GND8: C121.2, C122.1, C123.-, C124.2, C125.-, C127.2, C128.2, C129.-, C130.-, C131.2, C132.2, C133.2, C134.2, C135.2, J41.6, J42.GND, J43.1, J44.GND, J44.GND2, JP143.4A, JP143.4B, JP144.2, JP144.3, JP149.GND, JP150.4, JP151.2, JP151.3, LED17.C, LED18.C, R117.1, R125.1, R126.1, S17.1, S17.2, TP51.P$1, U25.3, U25.5, U25.21, U26.2, U27.1, Y17.2, Y18.2, Y18.4
GND9: C136.2, C137.1, C138.-, C139.2, C140.-, C142.2, C143.2, C144.-, C145.-, C146.2, C147.2, C148.2, C149.2, C150.2, J46.6, J47.GND, J48.1, J49.GND, J49.GND2, JP160.4A, JP160.4B, JP161.2, JP161.3, JP166.GND, JP167.4, JP168.2, JP168.3, LED19.C, LED20.C, R131.1, R139.1, R140.1, S19.1, S19.2, TP57.P$1, U28.3, U28.5, U28.21, U29.2, U30.1, Y19.2, Y20.2, Y20.4
INSERT: J3.P$4, Q1.1, R4.1
INSERT1: J7.P$4, Q4.1, R18.1
INSERT2: J12.P$4, Q7.1, R32.1
INSERT3: J17.P$4, Q10.1, R46.1
INSERT4: J22.P$4, Q13.1, R60.1
INSERT5: J27.P$4, Q16.1, R74.1
INSERT6: J32.P$4, Q19.1, R88.1
INSERT7: J37.P$4, Q22.1, R102.1
INSERT8: J42.P$4, Q25.1, R116.1
INSERT9: J47.P$4, Q28.1, R130.1
LV_SCL: J4.4, Q2.2, R11.1
LV_SCL1: J8.4, Q5.2, R21.1
LV_SCL2: J13.4, Q8.2, R35.1
LV_SCL3: J18.4, Q11.2, R49.1
LV_SCL4: J23.4, Q14.2, R63.1
LV_SCL5: J28.4, Q17.2, R77.1
LV_SCL6: J33.4, Q20.2, R91.1
LV_SCL7: J38.4, Q23.2, R105.1
LV_SCL8: J43.4, Q26.2, R119.1
LV_SCL9: J48.4, Q29.2, R133.1
LV_SDA: J4.3, Q3.2, R5.1
LV_SDA1: J8.3, Q6.2, R25.1
LV_SDA2: J13.3, Q9.2, R39.1
LV_SDA3: J18.3, Q12.2, R53.1
LV_SDA4: J23.3, Q15.2, R67.1
LV_SDA5: J28.3, Q18.2, R81.1
LV_SDA6: J33.3, Q21.2, R95.1
LV_SDA7: J38.3, Q24.2, R109.1
LV_SDA8: J43.3, Q27.2, R123.1
LV_SDA9: J48.3, Q30.2, R137.1
unnamed: LED1.A, R1.2
unnamed: LED2.A, R2.1
unnamed: U4.7, Y1.1
unnamed: U4.8, Y1.3
unnamed: D2.A, R16.1
unnamed: C17.1, U1.4
unnamed: Q2.3, QW1.2, R13.1
unnamed: C9.1, U1.7, Y2.1
unnamed: D3.A, R12.1
unnamed: C7.1, U1.8, Y2.3
unnamed: LED3.A, R10.1
unnamed: LED4.A, R9.2
unnamed: IC1.1, R19.2, R20.1
unnamed: U2.7, Y3.1
unnamed: IC3.1, R14.2, R15.1
unnamed: U2.8, Y3.3
unnamed: D6.A, R24.1
unnamed: D5.A, R23.1
unnamed: C27.1, U6.4
unnamed: Q5.3, QW4.2, R22.1
unnamed: Q6.3, QW3.2, R26.1
unnamed: C30.1, U6.7, Y4.1
unnamed: C29.1, U6.8, Y4.3
unnamed: LED5.A, R30.1
unnamed: LED6.A, R29.2
unnamed: IC2.1, R33.2, R34.1
unnamed: U7.7, Y5.1
unnamed: U7.8, Y5.3
unnamed: D9.A, R38.1
unnamed: D8.A, R37.1
unnamed: C42.1, U9.4
unnamed: Q8.3, QW6.2, R36.1
unnamed: Q9.3, QW5.2, R40.1
unnamed: C45.1, U9.7, Y6.1
unnamed: C44.1, U9.8, Y6.3
unnamed: LED7.A, R44.1
unnamed: LED8.A, R43.2
unnamed: IC4.1, R47.2, R48.1
unnamed: U10.7, Y7.1
unnamed: U10.8, Y7.3
unnamed: D12.A, R52.1
unnamed: D11.A, R51.1
unnamed: C57.1, U12.4
unnamed: Q11.3, QW8.2, R50.1
unnamed: Q3.3, QW2.2, R6.1
unnamed: Q12.3, QW7.2, R54.1
unnamed: C60.1, U12.7, Y8.1
unnamed: C59.1, U12.8, Y8.3
unnamed: LED9.A, R58.1
unnamed: LED10.A, R57.2
unnamed: IC5.1, R61.2, R62.1
unnamed: U13.7, Y9.1
unnamed: U13.8, Y9.3
unnamed: D15.A, R66.1
unnamed: D14.A, R65.1
unnamed: C72.1, U15.4
unnamed: Q14.3, QW10.2, R64.1
unnamed: Q15.3, QW9.2, R68.1
unnamed: C75.1, U15.7, Y10.1
unnamed: C74.1, U15.8, Y10.3
unnamed: LED11.A, R72.1
unnamed: LED12.A, R71.2
unnamed: IC6.1, R75.2, R76.1
unnamed: U16.7, Y11.1
unnamed: U16.8, Y11.3
unnamed: D18.A, R80.1
unnamed: D17.A, R79.1
unnamed: C87.1, U18.4
unnamed: Q17.3, QW12.2, R78.1
unnamed: Q18.3, QW11.2, R82.1
unnamed: C90.1, U18.7, Y12.1
unnamed: C89.1, U18.8, Y12.3
unnamed: LED13.A, R86.1
unnamed: LED14.A, R85.2
unnamed: IC7.1, R89.2, R90.1
unnamed: U19.7, Y13.1
unnamed: U19.8, Y13.3
unnamed: D21.A, R94.1
unnamed: D20.A, R93.1
unnamed: C102.1, U21.4
unnamed: Q20.3, QW14.2, R92.1
unnamed: Q21.3, QW13.2, R96.1
unnamed: C105.1, U21.7, Y14.1
unnamed: C104.1, U21.8, Y14.3
unnamed: LED15.A, R100.1
unnamed: LED16.A, R99.2
unnamed: IC8.1, R103.2, R104.1
unnamed: U22.7, Y15.1
unnamed: U22.8, Y15.3
unnamed: D24.A, R108.1
unnamed: D23.A, R107.1
unnamed: C117.1, U24.4
unnamed: Q23.3, QW16.2, R106.1
unnamed: Q24.3, QW15.2, R110.1
unnamed: C120.1, U24.7, Y16.1
unnamed: C119.1, U24.8, Y16.3
unnamed: LED17.A, R114.1
unnamed: LED18.A, R113.2
unnamed: IC9.1, R117.2, R118.1
unnamed: U25.7, Y17.1
unnamed: U25.8, Y17.3
unnamed: D27.A, R122.1
unnamed: D26.A, R121.1
unnamed: C132.1, U27.4
unnamed: Q26.3, QW18.2, R120.1
unnamed: Q27.3, QW17.2, R124.1
unnamed: C135.1, U27.7, Y18.1
unnamed: C134.1, U27.8, Y18.3
unnamed: LED19.A, R128.1
unnamed: LED20.A, R127.2
unnamed: IC10.1, R131.2, R132.1
unnamed: U28.7, Y19.1
unnamed: U28.8, Y19.3
unnamed: D30.A, R136.1
unnamed: D29.A, R135.1
unnamed: C147.1, U30.4
unnamed: Q29.3, QW20.2, R134.1
unnamed: Q30.3, QW19.2, R138.1
unnamed: C150.1, U30.7, Y20.1
unnamed: C149.1, U30.8, Y20.3
PWRIN: D1.A, J3.VIN0
PWRIN1: D4.A, J7.VIN0
PWRIN2: D7.A, J12.VIN0
PWRIN3: D10.A, J17.VIN0
PWRIN4: D13.A, J22.VIN0
PWRIN5: D16.A, J27.VIN0
PWRIN6: D19.A, J32.VIN0
PWRIN7: D22.A, J37.VIN0
PWRIN8: D25.A, J42.VIN0
PWRIN9: D28.A, J47.VIN0
RX-I: D3.C, JP11.1, JP19.1, U1.2, U4.30
RX-I1: D5.C, JP28.1, JP34.1, U2.30, U6.2
RX-I2: D8.C, JP45.1, JP51.1, U7.30, U9.2
RX-I3: D11.C, JP62.1, JP68.1, U10.30, U12.2
RX-I4: D14.C, JP79.1, JP85.1, U13.30, U15.2
RX-I5: D17.C, JP96.1, JP102.1, U16.30, U18.2
RX-I6: D20.C, JP113.1, JP119.1, U19.30, U21.2
RX-I7: D23.C, JP130.1, JP136.1, U22.30, U24.2
RX-I8: D26.C, JP147.1, JP153.1, U25.30, U27.2
RX-I9: D29.C, JP164.1, JP170.1, U28.30, U30.2
SCK: J2.3, JP2.5A, JP2.5B, JP12.5, R1.1, TP5.P$1, U4.17
SCK1: J6.3, JP24.5A, JP24.5B, JP31.5, R9.1, TP11.P$1, U2.17
SCK2: J11.3, JP41.5A, JP41.5B, JP48.5, R29.1, TP17.P$1, U7.17
SCK3: J16.3, JP58.5A, JP58.5B, JP65.5, R43.1, TP23.P$1, U10.17
SCK4: J21.3, JP75.5A, JP75.5B, JP82.5, R57.1, TP29.P$1, U13.17
SCK5: J26.3, JP92.5A, JP92.5B, JP99.5, R71.1, TP35.P$1, U16.17
SCK6: J31.3, JP109.5A, JP109.5B, JP116.5, R85.1, TP41.P$1, U19.17
SCK7: J36.3, JP126.5A, JP126.5B, JP133.5, R99.1, TP47.P$1, U22.17
SCK8: J41.3, JP143.5A, JP143.5B, JP150.5, R113.1, TP53.P$1, U25.17
SCK9: J46.3, JP160.5A, JP160.5B, JP167.5, R127.1, TP59.P$1, U28.17
SHLD: J5.SHLD1, J5.SHLD2, J5.SHLD3, J5.SHLD4
SHLD1: J9.SHLD1, J9.SHLD2, J9.SHLD3, J9.SHLD4
SHLD2: J14.SHLD1, J14.SHLD2, J14.SHLD3, J14.SHLD4
SHLD3: J19.SHLD1, J19.SHLD2, J19.SHLD3, J19.SHLD4
SHLD4: J24.SHLD1, J24.SHLD2, J24.SHLD3, J24.SHLD4
SHLD5: J29.SHLD1, J29.SHLD2, J29.SHLD3, J29.SHLD4
SHLD6: J34.SHLD1, J34.SHLD2, J34.SHLD3, J34.SHLD4
SHLD7: J39.SHLD1, J39.SHLD2, J39.SHLD3, J39.SHLD4
SHLD8: J44.SHLD1, J44.SHLD2, J44.SHLD3, J44.SHLD4
SHLD9: J49.SHLD1, J49.SHLD2, J49.SHLD3, J49.SHLD4
TX-O: D2.C, JP11.2, JP19.2, U1.3, U4.31
TX-O1: D6.C, JP28.2, JP34.2, U2.31, U6.3
TX-O2: D9.C, JP45.2, JP51.2, U7.31, U9.3
TX-O3: D12.C, JP62.2, JP68.2, U10.31, U12.3
TX-O4: D15.C, JP79.2, JP85.2, U13.31, U15.3
TX-O5: D18.C, JP96.2, JP102.2, U16.31, U18.3
TX-O6: D21.C, JP113.2, JP119.2, U19.31, U21.3
TX-O7: D24.C, JP130.2, JP136.2, U22.31, U24.3
TX-O8: D27.C, JP147.2, JP153.2, U25.31, U27.3
TX-O9: D30.C, JP164.2, JP170.2, U28.31, U30.3
USBVCC: BYP.2, C12.1, C15.+, F2.2, Q1.3
USBVCC1: BYP1.2, C23.1, C24.+, F1.2, Q4.3
USBVCC2: BYP2.2, C38.1, C39.+, F3.2, Q7.3
USBVCC3: BYP3.2, C53.1, C54.+, F4.2, Q10.3
USBVCC4: BYP4.2, C68.1, C69.+, F5.2, Q13.3
USBVCC5: BYP5.2, C83.1, C84.+, F6.2, Q16.3
USBVCC6: BYP6.2, C98.1, C99.+, F7.2, Q19.3
USBVCC7: BYP7.2, C113.1, C114.+, F8.2, Q22.3
USBVCC8: BYP8.2, C128.1, C129.+, F9.2, Q25.3
USBVCC9: BYP9.2, C143.1, C144.+, F10.2, Q28.3
VCC: C2.2, C18.1, J2.2, JP10.7, JP15.7, R2.2, R3.2, R6.2, R12.2, R13.2, R16.2, S2.2, S2.5, TP1.P$1, U1.16, U4.4, U4.6, U4.18
VCC1: C13.2, C28.1, J6.2, JP25.7, JP32.7, R10.2, R17.2, R22.2, R23.2, R24.2, R26.2, S4.2, S4.5, TP7.P$1, U2.4, U2.6, U2.18, U6.16
VCC2: C32.2, C43.1, J11.2, JP42.7, JP49.7, R30.2, R31.2, R36.2, R37.2, R38.2, R40.2, S6.2, S6.5, TP13.P$1, U7.4, U7.6, U7.18, U9.16
VCC3: C47.2, C58.1, J16.2, JP59.7, JP66.7, R44.2, R45.2, R50.2, R51.2, R52.2, R54.2, S8.2, S8.5, TP19.P$1, U10.4, U10.6, U10.18, U12.16
VCC4: C62.2, C73.1, J21.2, JP76.7, JP83.7, R58.2, R59.2, R64.2, R65.2, R66.2, R68.2, S10.2, S10.5, TP25.P$1, U13.4, U13.6, U13.18, U15.16
VCC5: C77.2, C88.1, J26.2, JP93.7, JP100.7, R72.2, R73.2, R78.2, R79.2, R80.2, R82.2, S12.2, S12.5, TP31.P$1, U16.4, U16.6, U16.18, U18.16
VCC6: C92.2, C103.1, J31.2, JP110.7, JP117.7, R86.2, R87.2, R92.2, R93.2, R94.2, R96.2, S14.2, S14.5, TP37.P$1, U19.4, U19.6, U19.18, U21.16
VCC7: C107.2, C118.1, J36.2, JP127.7, JP134.7, R100.2, R101.2, R106.2, R107.2, R108.2, R110.2, S16.2, S16.5, TP43.P$1, U22.4, U22.6, U22.18, U24.16
VCC8: C122.2, C133.1, J41.2, JP144.7, JP151.7, R114.2, R115.2, R120.2, R121.2, R122.2, R124.2, S18.2, S18.5, TP49.P$1, U25.4, U25.6, U25.18, U27.16
VCC9: C137.2, C148.1, J46.2, JP161.7, JP168.7, R128.2, R129.2, R134.2, R135.2, R136.2, R138.2, S20.2, S20.5, TP55.P$1, U28.4, U28.6, U28.18, U30.16
VIN: C5.+, D1.C, IC3.3, JP10.1, JP15.1
VIN1: C20.+, D4.C, IC1.3, JP25.1, JP32.1
VIN2: C35.+, D7.C, IC2.3, JP42.1, JP49.1
VIN3: C50.+, D10.C, IC4.3, JP59.1, JP66.1
VIN4: C65.+, D13.C, IC5.3, JP76.1, JP83.1
VIN5: C80.+, D16.C, IC6.3, JP93.1, JP100.1
VIN6: C95.+, D19.C, IC7.3, JP110.1, JP117.1
VIN7: C110.+, D22.C, IC8.3, JP127.1, JP134.1
VIN8: C125.+, D25.C, IC9.3, JP144.1, JP151.1
VIN9: C140.+, D28.C, IC10.3, JP161.1, JP168.1
VUSB: BYP.1, C10.1, F2.1, J5.VBUS1, J5.VBUS2, JP14.VBUS
VUSB1: BYP1.1, C22.1, F1.1, J9.VBUS1, J9.VBUS2, JP30.VBUS
VUSB2: BYP2.1, C37.1, F3.1, J14.VBUS1, J14.VBUS2, JP47.VBUS
VUSB3: BYP3.1, C52.1, F4.1, J19.VBUS1, J19.VBUS2, JP64.VBUS
VUSB4: BYP4.1, C67.1, F5.1, J24.VBUS1, J24.VBUS2, JP81.VBUS
VUSB5: BYP5.1, C82.1, F6.1, J29.VBUS1, J29.VBUS2, JP98.VBUS
VUSB6: BYP6.1, C97.1, F7.1, J34.VBUS1, J34.VBUS2, JP115.VBUS
VUSB7: BYP7.1, C112.1, F8.1, J39.VBUS1, J39.VBUS2, JP132.VBUS
VUSB8: BYP8.1, C127.1, F9.1, J44.VBUS1, J44.VBUS2, JP149.VBUS
VUSB9: BYP9.1, C142.1, F10.1, J49.VBUS1, J49.VBUS2, JP166.VBUS

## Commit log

2021-04-06 Initial commit
    Copy files from the RedBoard Repo
2021-04-07 Change to blackboard files
2021-04-07 started redboard logo in library
2021-04-08 Rename files to "RedBoard"
2021-04-08 Go through DRC errors
    Updated power MOSFET to be capable of 4.2A
    Broke out A6 and A7 pins to headers
2021-04-12 Update silkscreen to vector buzzard labels
    Working on making logo vector
2021-04-13 Finished vectorizing redboard logo. Updated board files
2021-04-13 Ran schematic and board auto-checklists
2021-04-13 Rename eagle files to "RedBoard_Plus"
2021-04-13 Remove reference layer from redboard logo. Remove layers 2 and 15 from board
2021-04-13 Pete's design review notes:
    SF logo on back
    GND vias next to USB C
    Remove 4-way nodes on sch
    Remove overlapping text on sch
    Move SFE logo in sch
    Sch typo
2021-04-13 Design review changes
2021-04-14 Switch CH340C for CH340G with external oscillator
2021-04-15 Update silkscreen
    Increased the size of PTH labels on back side to all be the same size
    Added "(PLUS)" label to board name - top/bottom
    Vector-ized "ELECTRONICS"
2021-04-15 Run checklist
2021-04-15 Change "I/O" label to "Logic" and make A4/A5 jumper labels inverted pill-shape
2021-04-16 Add "DNP" to headers on schematic
2021-04-19 QC Double check changes
2021-04-19 Update "GND" Buzzard labels
2021-04-19 Follow Up review changes
    Added Qwiic logo device to schematic
    Switch RXO/TXI signals at CH340G. Switched the order of LEDs as well
    Updated headers to use current library parts
    Updated ISP header sch symbol to use COPI/CIPO
2021-04-19 Generate CAM files
2021-04-22 Update prod_id on isp header
2021-05-10 Add test scripts
2021-05-13 Run engineering checklist
    Changes made:
    Flipped the V10 on the board edge
    Changed the 2 VCC flags in the schematic to power symbols
    Added the RedBoard logo to the SF Aesthetics library and replaced the device in the schematic
2021-05-13 Add the Arduino attribution to the board file and redraw dimensions
2021-05-14 Update silk on bottom of board
    Move "1" label more in-line with others
    Add "~" to pins 10 and 11
2021-05-14 Remove CAM files for single PCB
2021-05-14 Panelize
2021-05-17 Update panel
2021-05-17 Re-panelize without fiducials moved to left+right corners
2021-07-02 Update RedBoard_Plus.brd
    Minor update to board file to that adds two more measurements for board dimensions
2021-07-02 Remove Outdated Graphical Datasheet
    - Removing the old Graphical Datasheet for the old RedBoard. The latest will be found on the repo for the Graphical Datasheets.
    - Minor update on README.md header
